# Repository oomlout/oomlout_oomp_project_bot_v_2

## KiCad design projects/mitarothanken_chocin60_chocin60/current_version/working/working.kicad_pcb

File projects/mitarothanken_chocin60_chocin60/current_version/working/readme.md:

# chocin60
 
## summary 
* id: mitarothanken_chocin60_chocin60
* user: mitarothanken
* name: chocin60
* board: chocin60
* repo: https://github.com/mitaroThanken/ChocIn60
* src_file_repo_kicad_pcb: ChocIn60.kicad_pcb
* src_file_repo_kicad_pcb_link: https://github.com/mitaroThanken/ChocIn60/tree/develop/ChocIn60.kicad_pcb

* src_file_repo_sch: ChocIn60.sch
* src_file_repo_sch_link: https://github.com/mitaroThanken/ChocIn60/tree/develop/ChocIn60.sch
* full details link: https://github.com/oomlout/oomlout_oomp_project_bot_v_2/tree/main/projects/mitarothanken_chocin60_chocin60/current_version/working

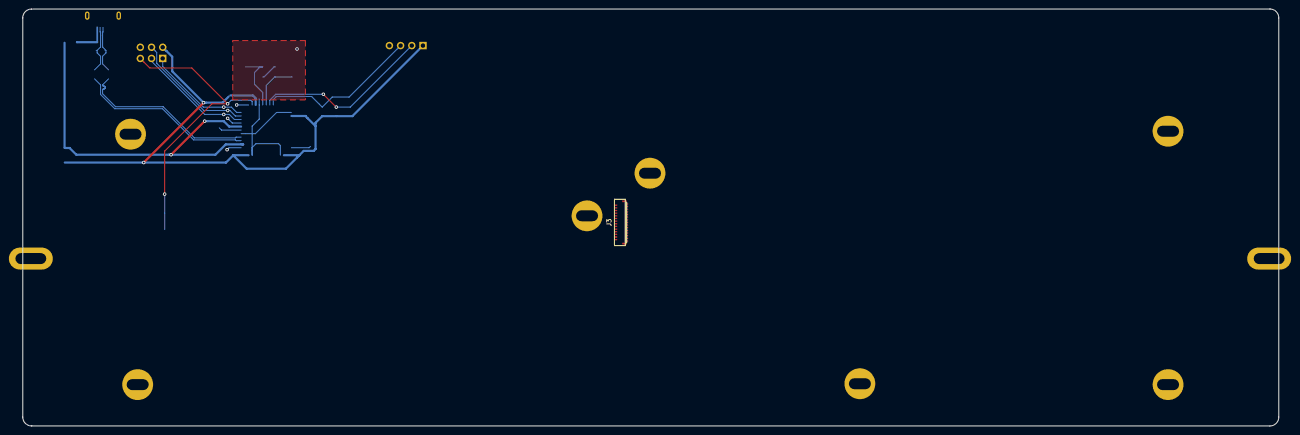
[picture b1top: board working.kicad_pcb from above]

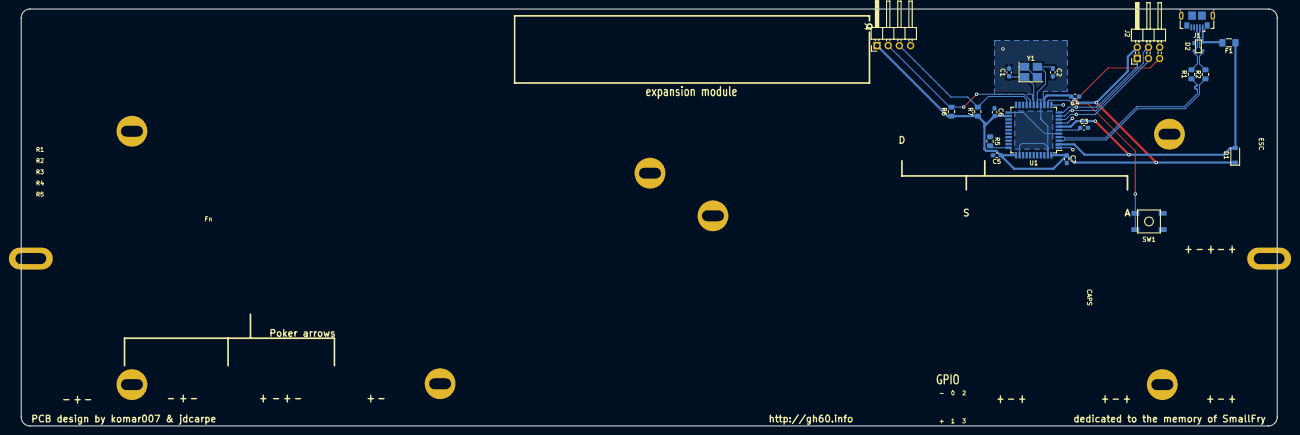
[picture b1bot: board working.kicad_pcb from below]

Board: 2 copper layers, 285.0 x 94.6 mm, 31 parts (21 on the bottom side), 38 nets.

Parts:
C1, C2: 22pF; C_0603_1608Metric_Pad1.05x0.95mm_HandSolder
C3: 1uF; C_0603_1608Metric_Pad1.05x0.95mm_HandSolder
C4, C5, C6: 0.1uF; C_0603_1608Metric_Pad1.05x0.95mm_HandSolder
C7: 10uF; C_0603_1608Metric_Pad1.05x0.95mm_HandSolder
D1: Schottky; D_SOD-123
D2: PRTR5V0U2X; SOT143B
F1: 500mA; Fuse_1206_3216Metric_Pad1.42x1.75mm_HandSolder
J1: USB_B_Micro; USB_Micro-B_GCT_USB3076-30-A
J2: AVR-ISP-6; PinHeader_2x03_P2.54mm_Horizontal
J3: FFC_FPC_Connectors_29POS; TE_1-2013496-0
J4: Conn_01x04; PinHeader_1x04_P2.54mm_Horizontal
R1, R2: 22; R_0805_2012Metric_Pad1.15x1.40mm_HandSolder
R5: 10k; R_0805_2012Metric_Pad1.15x1.40mm_HandSolder
R6, R7: 4.7k; R_0805_2012Metric_Pad1.15x1.40mm_HandSolder
S1, S2, S3: Screw; PKRH
S4, S5: Screw; PKRHSL
S6, S7, S8, S9: Screw_Tofu; PKRH
SW1: SW_Push; SKQGADE010
U1: ATmega32U4-AU; TQFP-44_10x10mm_P0.8mm
Y1: 16MHz; Crystal_SMD_3225-4Pin_3.2x2.5mm_HandSoldering

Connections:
+5V: C4.2, C5.1, C6.2, C7.1, D1.1, J2.2, J3.1, J3.2, J3.3, J4.1, R6.1, R7.1, U1.14, U1.24, U1.34, U1.44
/DN: D2.3, J1.2, R2.2
/DP: D2.2, J1.3, R1.2
D+: R1.1, U1.4
D-: R2.1, U1.3
GND: C1.2, C2.2, C3.2, C4.1, C5.2, C6.1, C7.2, D2.1, J1.5, J1.6, J2.6, J3.29, J4.4, R5.1, S1.1, S2.1, S3.1, S4.1, S5.1, S6.1, S7.1, S8.1, S9.1, SW1.1, SW1.3, U1.5, U1.15, U1.23, U1.35, U1.43, Y1.2, Y1.4
unnamed: C1.1, U1.17, Y1.1
unnamed: C2.1, U1.16, Y1.3
unnamed: C3.1, U1.6
unnamed: R5.2, U1.33
PB0: J3.4, U1.8
PB1_SCK: J2.3, J3.5, U1.9
PB2_MOSI: J2.4, J3.6, U1.10
PB3_MISO: J2.1, J3.7, U1.11
PB4: J3.8, U1.28
PB5: J3.9, U1.29
PB6: J3.10, U1.30
PB7: J3.11, U1.12
PC6: J3.12, U1.31
PC7: J3.13, U1.32
PD0_SCL: J3.14, J4.2, R6.2, U1.18
PD1_SDA: J3.15, J4.3, R7.2, U1.19
PD2: J3.16, U1.20
PD3: J3.17, U1.21
PD4: J3.18, U1.25
PD5: J3.19, U1.22
PD6: J3.20, U1.26
PD7: J3.21, U1.27
PE6: J3.22, U1.1
PF0: J3.23, U1.41
PF1: J3.24, U1.40
PF4: J3.25, U1.39
PF5: J3.26, U1.38
PF6: J3.27, U1.37
PF7: J3.28, U1.36
VBUS: D1.2, F1.1, U1.2, U1.7
VCC: D2.4, F1.2, J1.1
~RESET: J2.5, SW1.2, SW1.4, U1.13
